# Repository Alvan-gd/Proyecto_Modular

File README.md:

# DAIDA Dispositivo de Asistencia Inteligente para Discapacidad Auditiva

Un proyecto avanzado de sistemas embebidos y TinyML diseñado para asistir a personas con discapacidad auditiva mediante la detección, cálculo espacial y clasificación de sonidos ambientales críticos. El sistema procesa el audio en tiempo real directamente en el dispositivo (*Edge AI*) y proporciona retroalimentación multisensorial inmediata.

Este proyecto abarca el ciclo de vida completo de desarrollo bajo la metodología del **Modelo V** (estándares INCOSE y VDI 2206), desde el Procesamiento Digital de Señales (DSP) e inferencia estocástica, hasta el diseño de un PCB a medida con estrictas restricciones físicas (latencia <= 150 ms, masa <= 300 g, límite de 11 pines GPIO).

---

## ✨ Características Principales
* **Clasificación Jerárquica de Audio:** Detección de ~20 clases de sonidos ambientales divididas en tres niveles paramétricos (*Aviso, Urgencia, Emergencia*).
* **Resolución Espacial (TDOA):** Cálculo de Dirección de Llegada del sonido con una resolución de 45° (8 cuadrantes).
* **Feedback Multisensorial:** 
  * **Háptico:** Patrones de vibración segregados vía bus I2C.
  * **Visual:** Pantalla SPI con íconos dinámicos y codificación cromática perimetral virtualizada.
* **Procesamiento de Baja Latencia:** Muestreo a 16 kHz y ejecución concurrente para garantizar una respuesta End-to-End <= 150 ms.

---

## 🏗️ Arquitectura del Sistema

La arquitectura implementa un enfoque de multiprocesamiento asimétrico (Dual Core) bajo FreeRTOS, segregando de forma estricta los mapas de memoria para garantizar el determinismo temporal en la ruta crítica del modelo de Inteligencia Artificial.

```mermaid
flowchart TD
    %% Definición de las Calles (Swimlanes)
    
    subgraph Entorno Físico
        E1((Sonido Externo))
        E2((Usuario percibe alerta))
    end

    subgraph Hardware y Periféricos
        H1[Micrófonos I2S INMP441]
        H2[Controlador DMA de Hardware]
        H3[Controlador Háptico I2C]
        H4[Pantalla SPI]
    end

    subgraph Core 0 SRAM: Ruta Crítica IA
        C0_1[Llenado de Búfer Circular DMA]
        C0_2{¿Búfer Completo?}
        C0_3[Algoritmo TDOA: Cálculo de Dirección]
        C0_4[DSP: FFT y Espectrograma de Mel]
        C0_5[Inferencia TinyML Multiclase]
        C0_6{¿Confianza > Umbral?}
        C0_7{¿Clase Relevante?}
        C0_8[Path Negativo: Descartar y Limpiar]
        C0_9[Empacar Vector de Tareas y Enviar a Queue]
    end

    subgraph Core 1 PSRAM: Interfaz y Gráficos
        C1_1[Esperar Evento en Cola RTOS]
        C1_2[Extraer Mensaje de Cola]
        C1_3[Mapear Icono desde Flash/PSRAM]
        C1_4[Mapear Comando Háptico]
        C1_5[Transmitir Datos a Buses]
    end

    %% Flujo de la señal
    E1 --> H1
    H1 -- "Audio a 16 kHz" --> H2
    H2 --> C0_1
    C0_1 --> C0_2
    
    %% Camino negativo del buffer
    C0_2 -- "No (Esperar)" --> C0_1
    
    %% Ruta principal
    C0_2 -- "Sí (Muestra lista)" --> C0_3
    C0_3 --> C0_4
    C0_4 --> C0_5
    C0_5 --> C0_6
    
    %% Caminos Negativos de Clasificación
    C0_6 -- "No (Baja Confianza / Ruido)" --> C0_8
    C0_6 -- "Sí" --> C0_7
    C0_7 -- "No (Clase Ignorada)" --> C0_8
    C0_8 -- "Reiniciar Ciclo" --> C0_1
    
    %% Camino Crítico (Emergencia/Aviso)
    C0_7 -- "Sí (Aviso/Urgencia/Emergencia)" --> C0_9
    
    %% Salto entre núcleos mediante FreeRTOS
    C0_9 -- "FreeRTOS Queue (No bloqueante)" --> C1_1
    
    %% Procesamiento del Core 1
    C1_1 --> C1_2
    C1_2 --> C1_3
    C1_2 --> C1_4
    C1_3 --> C1_5
    C1_4 --> C1_5
    
    %% Salida física
    C1_5 -- "Trama I2C Hex" --> H3
    C1_5 -- "Trama SPI (Bitmap)" --> H4
    H3 --> E2
    H4 --> E2
    
    %% Estilos visuales
    classDef hardware fill:#f9f,stroke:#333,stroke-width:2px;
    classDef core0 fill:#bbf,stroke:#333,stroke-width:2px;
    classDef core1 fill:#bfb,stroke:#333,stroke-width:2px;
    
    class H1,H2,H3,H4 hardware;
    class C0_1,C0_2,C0_3,C0_4,C0_5,C0_6,C0_7,C0_8,C0_9 core0;
    class C1_1,C1_2,C1_3,C1_4,C1_5 core1;
```

## 🛠️ Stack Tecnológico y Hardware

### Hardware (Dominio Físico)
* **SoC:** Seeed Studio XIAO ESP32-S3 (Xtensa Dual-Core LX7 a 240 MHz, 8MB Flash, 8MB PSRAM).
* **Captura Acústica:** 4x Micrófonos INMP441 (Bus I2S Maestro-Esclavo).
* **Actuador Háptico:** Driver DRV2605L (Bus I2C).
* **Interfaz Visual:** Pantalla TFT/OLED (Bus SPI).

### Software (Dominio Lógico y MLOps)
* **RTOS & Framework:** FreeRTOS sobre ESP-IDF (C/C++).
* **Machine Learning:** Edge Impulse (Exportación optimizada para instrucciones vectoriales Xtensa LX7).
* **Entorno de Desarrollo:** Visual Studio Code + Docker (Contenedor inmutable para compilación cruzada).
* **Diseño EDA:** Proteus Design Suite (Ruteo de Carrier Board PCB).

---

## 📈 Estado Actual (Roadmap)
- [x] Definición de Requerimientos del Sistema (REQ-01 a REQ-08).
- [x] Diseño de Arquitectura (Hardware, Memoria y RTOS).
- [x] Diseño Detallado y Pruebas de Integración (TDOA y DSP).
- [x] Implementación de Firmware y Cuantización del Modelo.
- [ ] Fabricación de PCB y Validación de Usuario.

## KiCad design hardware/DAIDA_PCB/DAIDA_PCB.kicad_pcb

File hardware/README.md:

# Hardware Design

This directory contains the electronic design of the wearable device, completely isolated from the firmware ecosystem. 

**Toolchain:** The PCB design is developed using **Proteus Design Suite** (ISIS for schematic capture, ARES for PCB layout), chosen for its streamlined workflow and integrated simulation capabilities during the prototyping phase.

**Directory Structure:**
* `/proteus_project`: Contains the main Proteus project files (`.pdsprj`), schematics, and local component libraries.
* `/exports`: PDF exports of the schematic and 3D visualization screenshots.
* `/gerbers`: (Ignored by Git) Fabrication files generated for the PCB manufacturer.

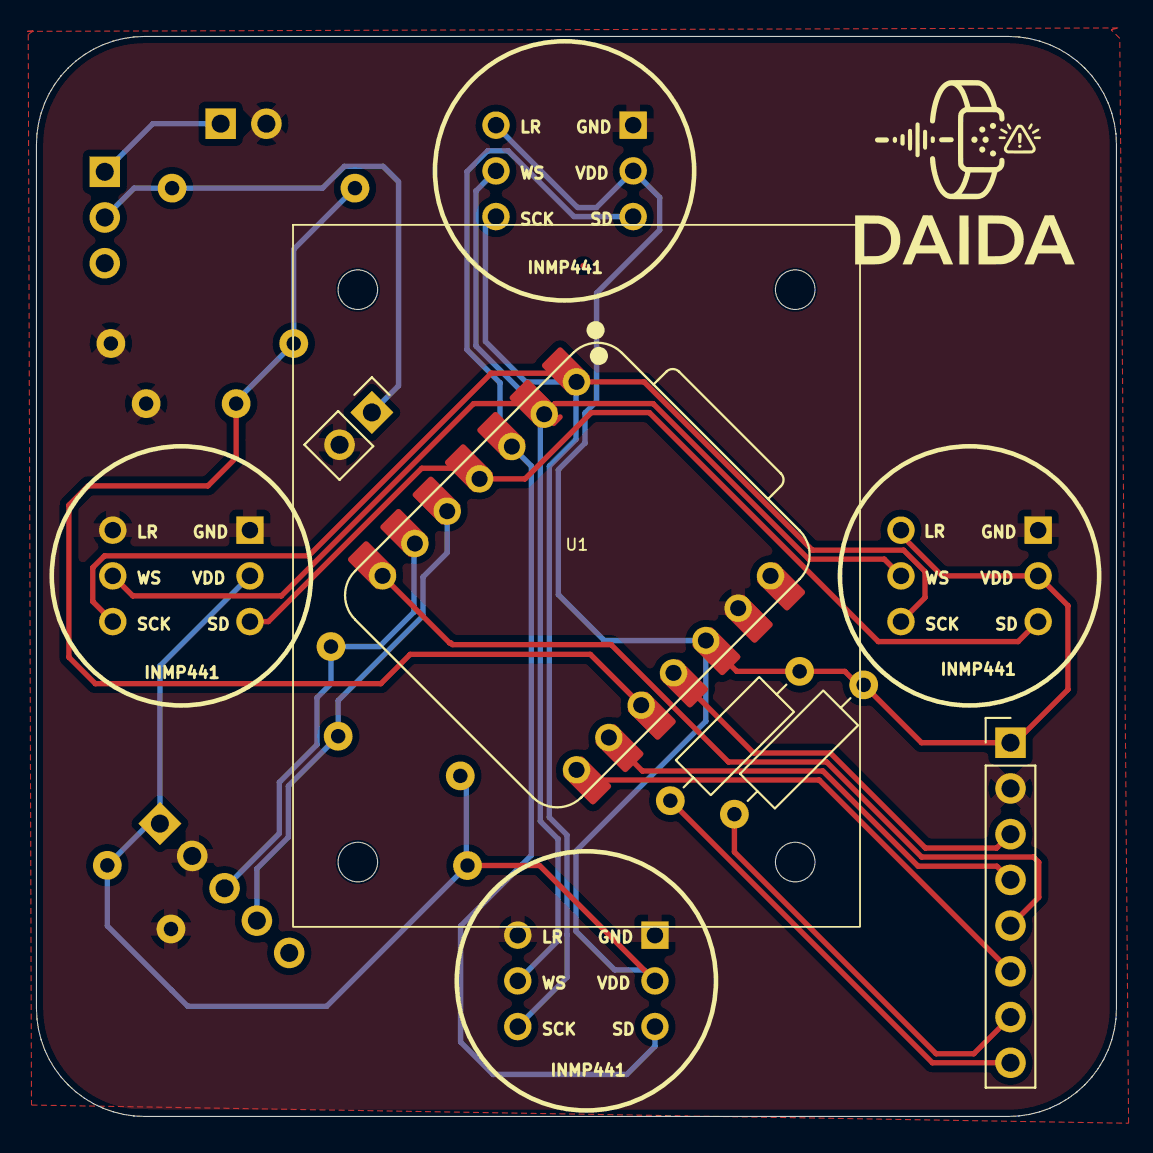
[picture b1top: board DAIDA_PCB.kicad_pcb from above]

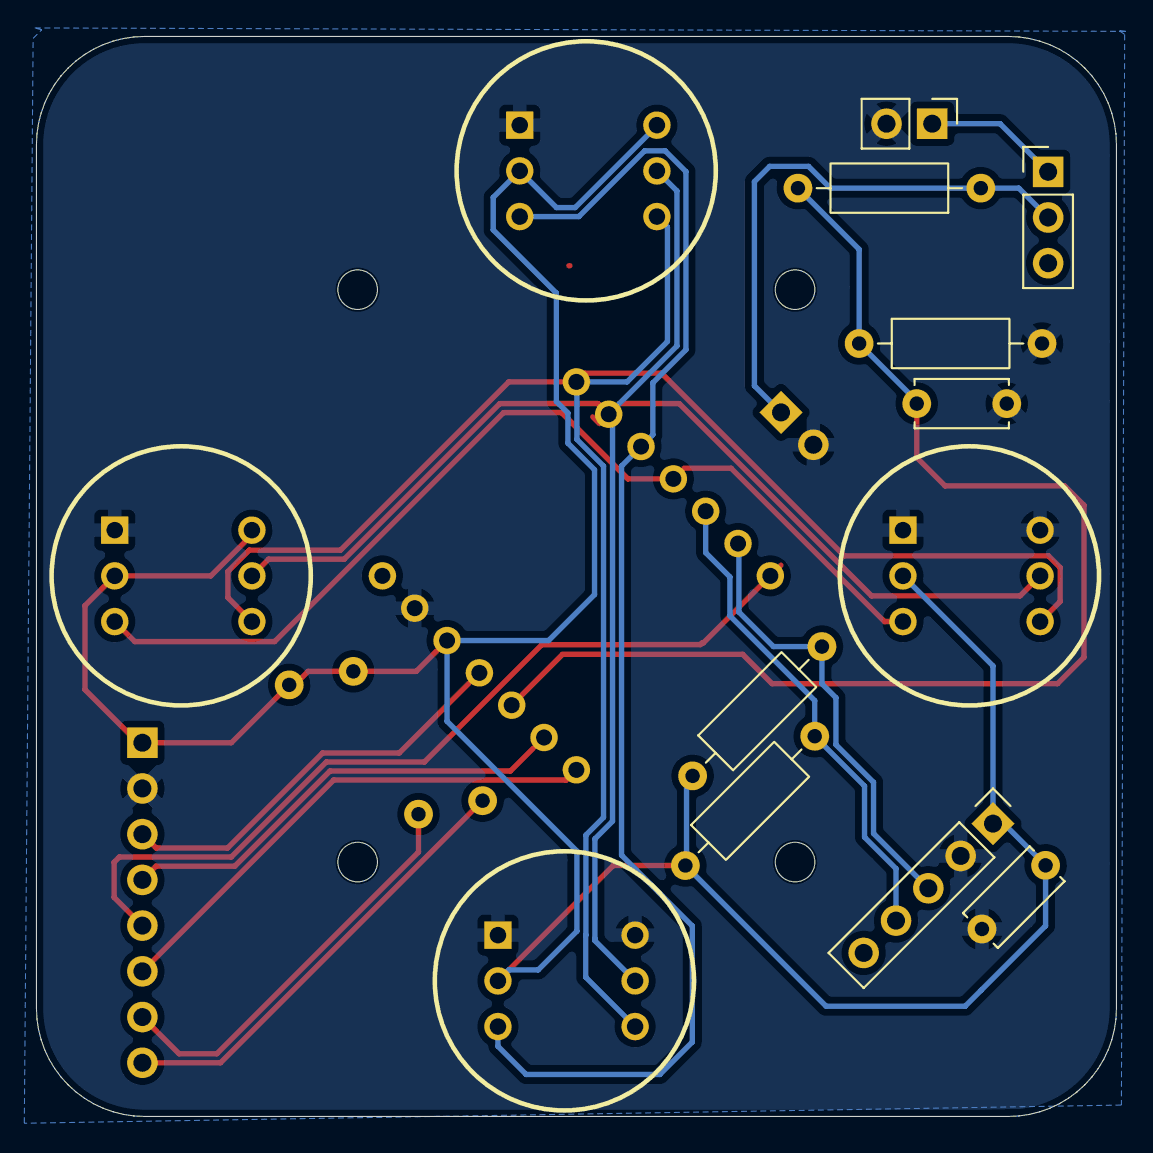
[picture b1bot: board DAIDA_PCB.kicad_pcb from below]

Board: 2 copper layers, 60.0 x 60.0 mm, 19 parts (9 on the bottom side), 17 nets.

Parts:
C1, C2: C; C_Disc_D5.0mm_W2.5mm_P5.00mm
J1: DRV2605L; PinHeader_1x05_P2.54mm_Vertical
J2: LCD ST7789V2; PinHeader_1x08_P2.54mm_Vertical
J3: Batery_xiao; PinHeader_1x02_P2.54mm_Vertical
J4: Batery; PinHeader_1x02_P2.54mm_Vertical
LCD: LCD_ST7789
R1, R2, R3, R4, R5, R6: R; R_Axial_DIN0207_L6.3mm_D2.5mm_P10.16mm_Horizontal
SW1: SW_SPDT; PinHeader_1x03_P2.54mm_Vertical
U1: XIAO-ESP32-S3; XIAO-ESP32-S3-DIP
U2, U3, U4, U5: INMP441 MODULE; INMP441_OMNIDIRECTIONAL_MICROPHONE_MODULE

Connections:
/3V: C2.2, J1.1, J2.1, R1.1, R2.1, R3.2, R4.2, U1.12 (3V3_OUT), U2.2 (SD), U2.6 (GND), U3.2 (SD), U4.2 (SD), U4.6 (GND), U5.2 (SD)
/BL: J2.8, R3.1
/CLK: J2.4, U1.9 (D8)
/CS: J2.5, U1.7 (D6)
/DC: J2.6, U1.8 (D7)
/DIN: J2.3, U1.11 (D10)
/RST: J2.7, R4.1
/SCL: J1.3, R1.2, U1.6 (D5)
/SDA: J1.4, R2.2, U1.5 (D4)
BAT+: J4.1, SW1.1 (A)
BAT_MEAS: C1.1, R5.2, R6.1, U1.10 (D9)
GND: C1.2, C2.1, J1.2, J2.2, J3.2, J4.2, R6.2, U1.13 (GND), U2.1 (SCK), U3.1 (SCK), U3.6 (GND), U4.1 (SCK), U5.1 (SCK), U5.6 (GND)
SCK: U1.1 (D0), U2.4 (L/R), U3.4 (L/R), U4.4 (L/R), U5.4 (L/R)
SD_1: U1.3 (D2), U2.3 (WS), U3.3 (WS)
SD_2: U1.4 (D3), U4.3 (WS), U5.3 (WS)
SW_BAT: J3.1, R5.1, SW1.2 (B)
WS: U1.2 (D1), U2.5 (GND), U3.5 (GND), U4.5 (GND), U5.5 (GND)

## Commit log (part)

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2026-06-14 Refactor README for improved structure and clarity
    Formatted and structured the README content for better readability and organization.
2026-06-14 Add bibliography
2026-06-15 Organizar documentos en carpetas
2026-06-15 Se añadio el gitignore
2026-06-15 Se añadio estructura de carpetas y READMEs
2026-06-15 README corregido
